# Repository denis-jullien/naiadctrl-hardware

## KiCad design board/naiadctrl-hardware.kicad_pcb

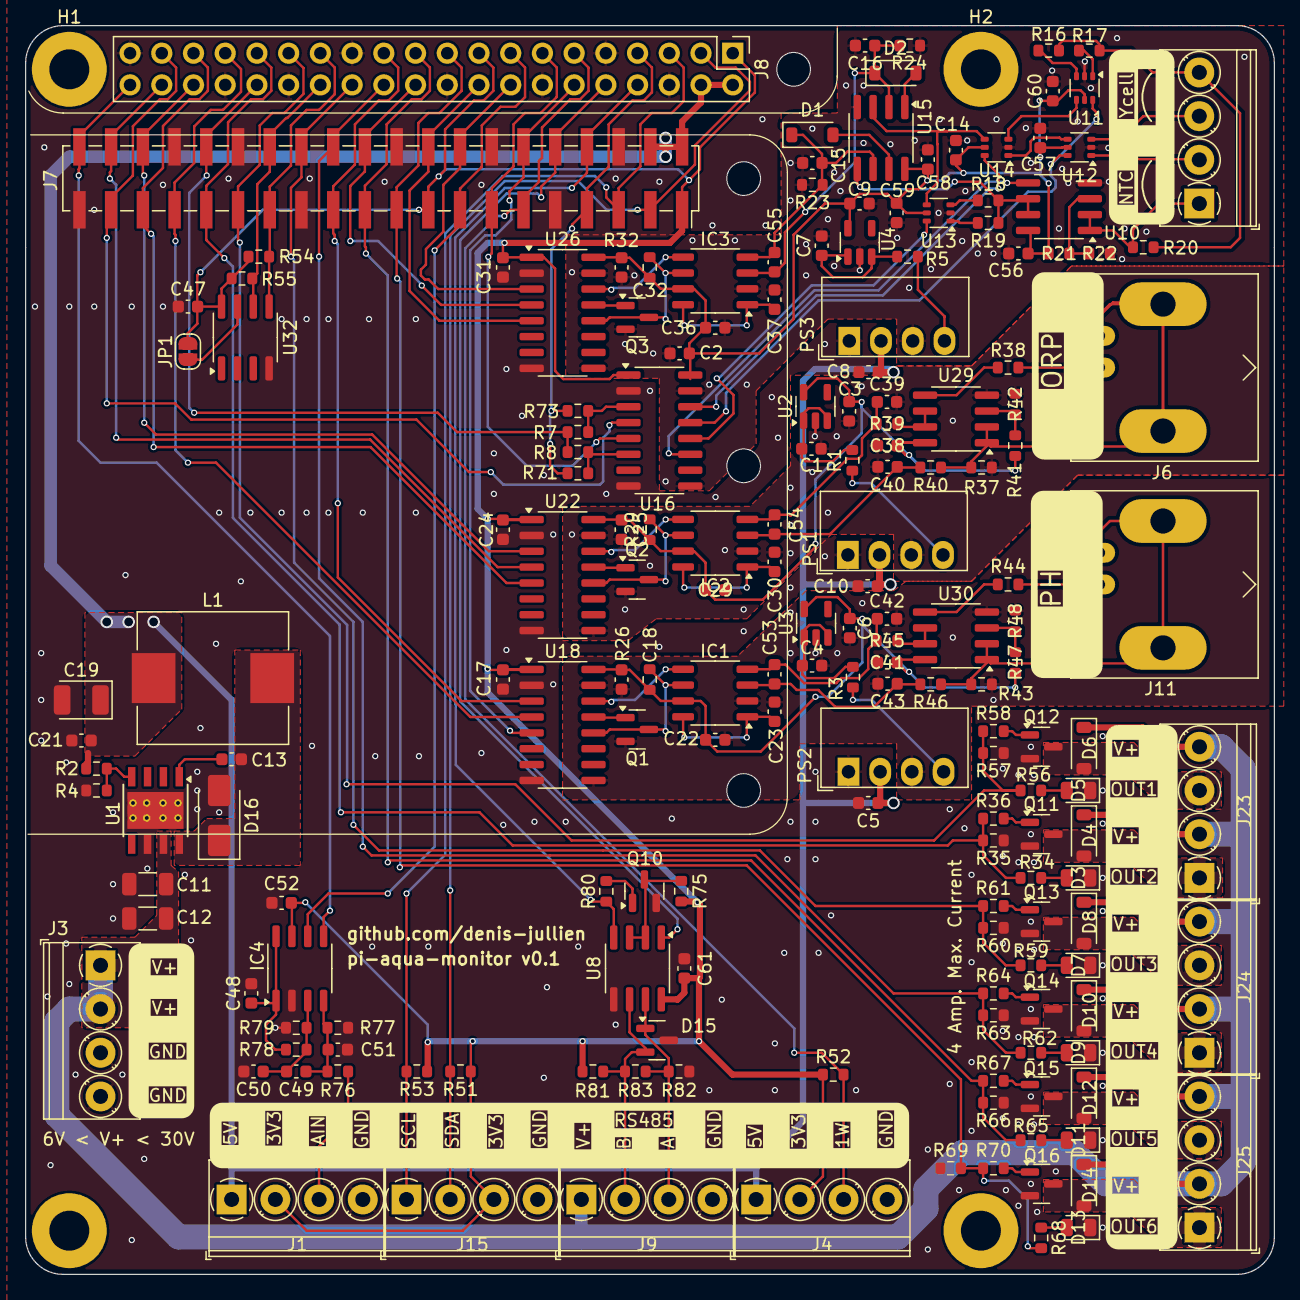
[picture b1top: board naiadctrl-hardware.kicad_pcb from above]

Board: 2 copper layers, 100.0 x 100.0 mm, 190 parts (0 on the bottom side), 123 nets.

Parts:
C1, C3, C4, C5, C6, C7, C8, C9, C10, C15, C16, C39, C40, C42, C43: 1u; C_0603_1608Metric
C2, C14, C17, C18, C21, C22, C23, C24, C25, C29, C30, C31, C32, C36, C37, C38, C41, C47, C48, C49, C50, C51, C52, C53, C54, C55, C56, C57, C58, C59, C60, C61: 0.1u; C_0603_1608Metric
C11, C12: 10u; C_1206_3216Metric
C13: 10n; C_0603_1608Metric
C19: 220u; CP_EIA-3528-21_Kemet-B
D1, D2, D4, D6, D8, D10, D12, D14: B5819W; D_SOD-123
D3, D5, D7, D9, D11, D13: LED; LED_0805_2012Metric
D15: PSM712-LF-T7; SOT-23
D16: SS54; D_SMA
H1, H2, H3, H4: MountingHole_Pad; MountingHole_3.2mm_M3_Pad
IC1, IC2, IC3, IC4: CS1237; SO-8_3.9x4.9mm_P1.27mm
J1, J2, J3, J4, J9, J15, J23, J24, J25: Conn_01x04; TerminalBlock_Phoenix_PT-1,5-4-3.5-H_1x04_P3.50mm_Horizontal
J6, J11: Conn_Coaxial; BNC_Amphenol_B6252HB-NPP3G-50_Horizontal
J7: GPIO; PinSocket_2x20_P2.54mm_Vertical_SMD
J8: GPIO; PinHeader_2x20_P2.54mm_Vertical
JP1: ID_WP; SolderJumper-2_P1.3mm_Open_RoundedPad1.0x1.5mm
L1: 15u; L_Chilisin_BMRF00101040
MH2, MH3, MH4, MH4#2: MountingHole_2.7mm_M2.5
PS1, PS2, PS3: B0505S-1W; Converter_DCDC_Murata_MEE1SxxxxSC_THT
Q1, Q2, Q3, Q10: 2N7002; SOT-23
Q11, Q12, Q13, Q14, Q15, Q16: AO3400A; SOT-23
R1, R3, R5, R36, R58, R61, R64, R67, R70, R80: 150; R_0603_1608Metric
R2, R17, R21, R22, R26, R29, R32, R35, R37, R39, R40, R41, R42, R43, R45, R46, R47, R48, R57, R60, R63, R66, R69, R75, R76, R77, R78, R79, R81, R82: 10k; R_0603_1608Metric
R4: 3.3k; R_0603_1608Metric
R7, R8, R71, R73: 0R; R_0603_1608Metric
R16, R18, R23, R24: 1k; R_0603_1608Metric
R19: 100k; R_0603_1608Metric
R20: 100R; R_0603_1608Metric
R34, R56, R59, R62, R65, R68: 560R; R_0603_1608Metric
R38, R44: 1M; R_0603_1608Metric
R51, R52, R53, R54, R55: 3.9k; R_0603_1608Metric
R83: 120R; R_0603_1608Metric
U1: TPS5430DDA; TI_SO-PowerPAD-8_ThermalVias
U2, U3, U4: ME6211C33M5G-N; SOT-23-5
U8: SP3485EN; SOIC-8_3.9x4.9mm_P1.27mm
U10, U15, U29, U30: LMC6482; SOIC-8_3.9x4.9mm_P1.27mm
U11, U12, U13, U14: ET3157; SOT-363_SC-70-6
U16: π140U31; SOIC-16_3.9x9.9mm_P1.27mm
U18, U22, U26: π131U31; SOIC-16_3.9x9.9mm_P1.27mm
U32: CAT24C64WI-GT3; SOIC-8_3.9x4.9mm_P1.27mm

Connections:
+3V3: C17.1, C24.1, C31.1, C47.1, C52.1, C61.1, IC4.7 (VDD), J1.2, J4.2, J7.1, J7.17, J8.1, J8.17, J15.3, JP1.2 (B), R51.1, R52.1, R53.1, R54.1, R55.1, R75.1, R81.1, U8.8 (VCC), U16.1 (VDD1), U18.1 (V_{CC1}), U22.1 (V_{CC1}), U26.1 (V_{CC1}), U32.8 (VCC)
+5V: C5.1, C8.1, C10.1, C19.1, C21.1, J1.1, J4.1, J7.2, J7.4, J8.2, J8.4, L1.2, PS1.2 (+Vin), PS2.2 (+Vin), PS3.2 (+Vin), R2.1
+12V: C11.2, C12.2, D4.1 (K), D6.1 (K), D8.1 (K), D10.1 (K), D12.1 (K), D14.1 (K), J3.1, J3.2, J9.1, J23.2, J23.4, J24.2, J24.4, J25.2, J25.4, U1.7 (VIN)
/Conductivity Mesurement 2/CLKIN: R8.2, R71.2, U16.6 (VID)
/Conductivity Mesurement 2/ISO_CLK: U10.5 (+), U16.11 (VOD)
/Conductivity Mesurement 2/ISO_RANGE: U13.6, U16.12 (VOC)
/Conductivity Mesurement 2/ISO_~CAL/MEAS: U14.6, U16.14 (VOA)
/Conductivity Mesurement 2/ISO_~TEMP/EC: U11.6, U12.6, U16.13 (VOB)
/Conductivity Mesurement 2/VOUTN: C16.1, C55.2, D2.1 (K), IC3.3 (AINN), R24.1, U15.2 (-)
/Conductivity Mesurement 2/VOUTP: C15.1, C55.1, D1.1 (K), IC3.4 (AINP), R23.1, U15.6 (-)
/Conductivity Mesurement 2/~CAL/MEAS: R7.2, R73.2, U16.3 (VIA)
/Isolated ADC1/ISO_3V3: C3.1, C25.1, C29.1, C38.1, IC2.7 (VDD), R29.1, R41.1, U2.5 (VOUT), U22.16 (V_{CC2}), U29.8 (V+)
/Isolated ADC1/ISO_ADCN: C40.1, C54.2, IC2.3 (AINN), R40.2
/Isolated ADC1/ISO_ADCP: C39.1, C54.1, IC2.4 (AINP), R39.2
/Isolated ADC1/ISO_GND: C1.2, C3.2, C25.2, C29.2, C30.2, C38.2, C39.2, C40.2, IC2.2 (GND), PS1.3 (-Vout), Q2.2 (S), R37.2, R42.2, U2.2 (GND), U22.9 (GND2), U22.15 (GND2), U29.4 (V-)
/Isolated ADC2/ISO_3V3: C2.1, C9.1, C14.1, C32.1, C36.1, C56.1, C57.1, C58.1, C59.1, C60.1, IC3.7 (VDD), R21.1, R32.1, U4.5 (VOUT), U10.8 (V+), U11.5 (V+), U12.5 (V+), U13.5 (V+), U14.5 (V+), U15.8 (V+), U16.16 (VDD2), U26.16 (V_{CC2})
/Isolated ADC2/ISO_GND: C2.2, C7.2, C9.2, C14.2, C15.2, C16.2, C32.2, C36.2, C37.2, C56.2, C57.2, C58.2, C59.2, C60.2, IC3.2 (GND), PS3.3 (-Vout), Q3.2 (S), R22.2, R23.2, R24.2, U4.2 (GND), U10.4 (V-), U11.2 (GND), U12.2 (GND), U13.2 (GND), U14.2 (GND), U15.4 (V-), U16.9 (GND2), U16.15 (GND2), U26.9 (GND2), U26.15 (GND2)
/Isolated ADC/ISO_3V3: C6.1, C18.1, C22.1, C41.1, IC1.7 (VDD), R26.1, R47.1, U3.5 (VOUT), U18.16 (V_{CC2}), U30.8 (V+)
/Isolated ADC/ISO_ADCN: C43.1, C53.2, IC1.3 (AINN), R46.2
/Isolated ADC/ISO_ADCP: C42.1, C53.1, IC1.4 (AINP), R45.2
/Isolated ADC/ISO_GND: C4.2, C6.2, C18.2, C22.2, C23.2, C41.2, C42.2, C43.2, IC1.2 (GND), PS2.3 (-Vout), Q1.2 (S), R43.2, R48.2, U3.2 (GND), U18.9 (GND2), U18.15 (GND2), U30.4 (V-)
/Motor 1/MOSFET: D6.2 (A), J23.3, Q12.3 (D)
/Motor 2/MOSFET: D4.2 (A), J23.1, Q11.3 (D)
/Motor 3/MOSFET: D8.2 (A), J24.3, Q13.3 (D)
/Motor 4/MOSFET: D10.2 (A), J24.1, Q14.3 (D)
/Motor 5/MOSFET: D12.2 (A), J25.3, Q15.3 (D)
/Motor 6/MOSFET: D14.2 (A), J25.1, Q16.3 (D)
/PI Headers/GPIO2/SDA1: J7.3, J8.3, J15.2, R51.2
/PI Headers/GPIO3/SCL1: J7.5, J8.5, J15.1, R53.2
/PI Headers/GPIO4/GPCLK0: J7.7, J8.7, R71.1, R73.1
/PI Headers/GPIO5: J7.29, J8.29, R56.2, R57.2, R58.1
/PI Headers/GPIO6: J7.31, J8.31, R34.2, R35.2, R36.1
/PI Headers/GPIO7/SPI0.CE1: J7.26, J8.26, R59.2, R60.2, R61.1
/PI Headers/GPIO8/SPI0.CE0: J7.24, J8.24, R62.2, R63.2, R64.1
/PI Headers/GPIO9/SPI0.MISO: J7.21, J8.21, R65.2, R66.2, R67.1
/PI Headers/GPIO10/SPI0.MOSI: J7.19, J8.19, R68.2, R69.2, R70.1
/PI Headers/GPIO11/SPI0.SCLK: J7.23, J8.23, U18.3 (INA)
/PI Headers/GPIO12/PWM0: J7.32, J8.32, R7.1, R8.1
/PI Headers/GPIO13/PWM1: J7.33, J8.33, U18.4 (INB)
/PI Headers/GPIO14/TXD0: J7.8, J8.8, R80.1, U8.4 (DI)
/PI Headers/GPIO15/RXD0: J7.10, J8.10, U8.1 (RO)
/PI Headers/GPIO16: J7.36, J8.36, U22.3 (INA)
/PI Headers/GPIO17: J4.3, J7.11, J8.11, R52.2
/PI Headers/GPIO18/PCM.CLK: J7.12, J8.12, U18.5 (OUTC)
/PI Headers/GPIO19/PCM.FS: J7.35, J8.35, U22.5 (OUTC)
/PI Headers/GPIO20/PCM.DIN: J7.38, J8.38, U22.4 (INB)
/PI Headers/GPIO21/PCM.DOUT: IC4.5 (SCLK), J7.40, J8.40
/PI Headers/GPIO22: IC4.6 (~DRDY~{/DOUT), J7.15, J8.15
/PI Headers/GPIO23: J7.16, J8.16, U26.3 (INA)
/PI Headers/GPIO24: J7.18, J8.18, U26.5 (OUTC)
/PI Headers/GPIO25: J7.22, J8.22, U26.4 (INB)
/PI Headers/GPIO26: J7.37, J8.37, U16.4 (VIB)
/PI Headers/GPIO27: J7.13, J8.13, U16.5 (VIC)
/PI Headers/ID_SCL: J7.28, J8.28, R55.2, U32.6 (SCL)
/PI Headers/ID_SDA: J7.27, J8.27, R54.2, U32.5 (SDA)
GND: C5.2, C8.2, C10.2, C11.1, C12.1, C17.2, C19.2, C21.2, C24.2, C31.2, C47.2, C48.2, C50.2, C51.2, C52.2, C61.2, D3.1 (K), D5.1 (K), D7.1 (K), D9.1 (K), D11.1 (K), D13.1 (K), D15.3 (A), D16.2 (A), IC4.2 (GND), J1.4, J3.3, J3.4, J4.4, J7.6, J7.9, J7.14, J7.20, J7.25, J7.30, J7.34, J7.39, J8.6, J8.9, J8.14, J8.20, J8.25, J8.30, J8.34, J8.39, J9.4, J15.4, PS1.1 (-Vin), PS2.1 (-Vin), PS3.1 (-Vin), Q10.2 (S), Q11.2 (S), Q12.2 (S), Q13.2 (S), Q14.2 (S), Q15.2 (S), Q16.2 (S), R4.2, R35.1, R57.1, R60.1, R63.1, R66.1, R69.1, R77.2, R79.2, R82.2, U1.6 (GND), U1.9 (GNDPAD), U8.5 (GND), U16.2 (GND1), U16.8 (GND1), U18.2 (GND1), U18.8 (GND1), U22.2 (GND1), U22.8 (GND1), U26.2 (GND1), U26.8 (GND1), U32.4 (GND)
unnamed: D1.2 (A), U15.7
unnamed: D2.2 (A), U15.1
unnamed: D3.2 (A), R34.1
unnamed: D5.2 (A), R56.1
unnamed: D7.2 (A), R59.1
unnamed: D9.2 (A), R62.1
unnamed: D11.2 (A), R65.1
unnamed: D13.2 (A), R68.1
unnamed: C13.2, D16.1 (K), L1.1, U1.8 (PH)
unnamed: C23.1, IC1.1 (REFIN), IC1.8 (REFOUT)
unnamed: IC1.5 (SCLK), U18.14 (OUTA)
unnamed: IC1.6 (~DRDY~{/DOUT), Q1.3 (D), R26.2, U18.12 (INC)
unnamed: C30.1, IC2.1 (REFIN), IC2.8 (REFOUT)
unnamed: IC2.5 (SCLK), U22.14 (OUTA)
unnamed: IC2.6 (~DRDY~{/DOUT), Q2.3 (D), R29.2, U22.12 (INC)
unnamed: C37.1, IC3.1 (REFIN), IC3.8 (REFOUT)
unnamed: IC3.5 (SCLK), U26.14 (OUTA)
unnamed: IC3.6 (~DRDY~{/DOUT), Q3.3 (D), R32.2, U26.12 (INC)
unnamed: C49.2, C50.1, IC4.3 (AINN), R78.2, R79.1
unnamed: C49.1, C51.1, IC4.4 (AINP), R76.2, R77.1
unnamed: C48.1, IC4.1 (REFIN), IC4.8 (REFOUT), R78.1
unnamed: J1.3, R76.1
unnamed: J2.1, R20.2, U10.1, U10.2 (-)
unnamed: J2.2, U12.1
unnamed: J2.3, U12.3
unnamed: J2.4, R16.1, R17.1, R20.1
unnamed: J6.2 (Ext), R37.1, R40.1, U29.1, U29.2 (-)
unnamed: J6.1 (In), R38.1
unnamed: D15.2 (K), J9.2, R81.2, R83.1, U8.6 (A)
unnamed: D15.1 (K), J9.3, R82.1, R83.2, U8.7 (B)
unnamed: J11.2 (Ext), R43.1, R46.1, U30.1, U30.2 (-)
unnamed: J11.1 (In), R44.1
unnamed: JP1.1 (A), U32.7 (WP)
unnamed: PS1.4 (+Vout), R1.1
unnamed: PS2.4 (+Vout), R3.1
unnamed: PS3.4 (+Vout), R5.1
unnamed: Q1.1 (G), U18.13 (OUTB)
unnamed: Q2.1 (G), U22.13 (OUTB)
unnamed: Q3.1 (G), U26.13 (OUTB)
unnamed: Q10.3 (D), R75.2, U8.2 (~RE), U8.3 (DE)
unnamed: Q10.1 (G), R80.2
unnamed: Q11.1 (G), R36.2
unnamed: Q12.1 (G), R58.2
unnamed: Q13.1 (G), R61.2
unnamed: Q14.1 (G), R64.2
unnamed: Q15.1 (G), R67.2
unnamed: Q16.1 (G), R70.2
unnamed: R16.2, U11.3
unnamed: R17.2, U11.1
unnamed: R18.2, U13.3
unnamed: R19.2, U13.1
unnamed: C13.1, U1.1 (BOOT)
unnamed: R2.2, R4.1, U1.4 (VSENSE)
unnamed: C1.1, R1.2, U2.1 (VIN), U2.3 (EN)
unnamed: C4.1, R3.2, U3.1 (VIN), U3.3 (EN)
unnamed: C7.1, R5.2, U4.1 (VIN), U4.3 (EN)
unnamed: R21.2, R22.1, U10.3 (+)
unnamed: R18.1, R19.1, U10.6 (-), U10.7, U15.5 (+)
unnamed: U11.4, U14.3
unnamed: U12.4, U14.1
unnamed: U13.4, U14.4, U15.3 (+)
unnamed: R41.2, R42.1, U29.3 (+)
unnamed: R38.2, U29.5 (+)
unnamed: R39.1, U29.6 (-), U29.7
unnamed: R47.2, R48.1, U30.3 (+)
unnamed: R44.2, U30.5 (+)
unnamed: R45.1, U30.6 (-), U30.7

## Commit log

2025-05-01 copy project
2025-05-02 move kicad files in baord/ folder
